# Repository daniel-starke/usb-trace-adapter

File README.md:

# USB Trace Adapter

The USB trace adapter can be used to trace/probe the USB communication of a
USB low speed, high speed or full speed connection with a logic analyzer
or oscilloscope.

# Structure

The USB trace adapter is build up of a USB 2.0 type A receptacle and
a USB 2.0 type A plug at both ends with a pin header in-between.
All lines are passed through between receptacle and plug as it.
The pin header offers easy access to VBUS, D+, D- and GND to allow
tracing and probing.

# Manufacturing

## PCB

Use the following parameters when ordering the PCB. Note that the values
have only been tested with JLCPCB so far. See [gerber files](hw/gerber).
- layers: 2
- base material: FR4
- dimensions: 21x18.8mm
- thickness: 1.6mm
- surface finish: lead free HASL
- impedance control: no
- outer copper weight: 1oz

With no special extras.

## BOM

- 1x [USB 2.0 type A plug](https://datasheet.lcsc.com/szlcsc/1811131825_Jing-Extension-of-the-Electronic-Co-C9739_C9739.pdf)
- 1x [USB 2.0 type A receptacle](https://datasheet.lcsc.com/lcsc/1912111437_SHOU-HAN-AF-90--WJDG_C456018.pdf)
- 1x [single row 4x pin header with 2.54mm pitch](https://datasheet.lcsc.com/lcsc/2008301604_Wcon-1125-1104G0S118C005_C721444.pdf)

All parts can be ordered at [LCSC](https://www.lcsc.com) (C9739, C456018 and C721444).

## Case

The case consists of a [bottom](print/case-Bottom.stl) and a
[top](print/case-Top.stl) part and can be 3D printed with PLA.
Other materials have not been tested.
Use the following print settings:
- layer height: 0.2mm
- nozzle diameter: 0.4mm
- infill: ≥15%
- perimeters: ≥3
- variable width perimeter generator (e.g. Arachne in PrusaSlicer)
- support: none
- print orientation: same as STL

Also recommended are:
- solid layers: ≥4
- infill pattern: adaptive cubic
- top/bottom fill pattern: monotonic

The [FreeCAD file](print/case.FCStd) contains a spreadsheet to easily change
tolerances to match the capabilities of the used 3D printer.

## Assembly

1. Solder the USB 2.0 type A plug at J1.
2. Solder the USB 2.0 type A receptacle at J2.
3. Solder the single row 4x pin header at J3.
4. Put the finished PCB into the bottom part of the case.
   The orientation is unambiguous.
   
5. Press the top part of the case onto the bottom part. Both parts should
   snap together. Make sure that the pin header hole is "pointing" towards the
   USB receptacle.

Note: All parts are soldered on the same side of the PCB.  
**Important:** Be sure that the USB connectors are fully inserted and
aligned when soldering. Especially when handling the USB plug.

## Connector Cable

It is possible to glue 4 female jumper cables and a small block of plastic
together to form a coded connector cable.

## Tracing

Sigrok provides ways to convert a logic trace into a PCAP file for further
analysis via Wireshark. See https://sigrok.org/blog/new-protocol-decoder-usb-request

### Example: Rigol DS1202Z-E with PulseView

This combination works fine for USB low speed (1.5 Mbps) and high speed (12 Mbps)
devices. However, it only captures a very short duration.

- Connect both probes to `D+` and `D-` and the ground to `GND`.
- Set the resolution to 5ms (trace length = 124ms, USB high speed) and the trigger to 1.5V.
- Set trigger type to `Pulse` on the channel with `D+` with less than 80ns.
- Run a single shot.
- Connect PulseView to Rigol DS1202Z-E and set its data source to `Memory`.
- Run the trace to collect the trace data.
- Set both channels to logic conversion via threshold (TTL).
- Add `USB request` decoder.

### Example: AZDelivery Logic Analyzer with sigrok

This combination works fine for USB low speed (1.5 Mbps) and may give some usable
results with USB high speed (12 Mbps) devices. Preferable is a logic analyzer with
48 MHz or more for USB high speed devices.

- Connect both probes to `D+` (CH0) and `D-` (CH1) and the ground to `GND`.
- `sigrok-cli -d fx2lafw -c samplerate=24M -C D0=DP,D1=DM --continuous -o trace.sr`.
- `sigrok-cli -i trace.sr -P usb_signalling:dp=DP:dm=DM,usb_packet,usb_request -B usb_request=pcap > trace.pcap`

Note that defining triggers does not work stable for this logic analyzer. The trace aborts shortly.

# License

See [LICENSE](LICENSE).  

# Contributions

No content contributions are accepted. Please file a bug report or feature request instead.  
This decision was made in consideration of the used license.

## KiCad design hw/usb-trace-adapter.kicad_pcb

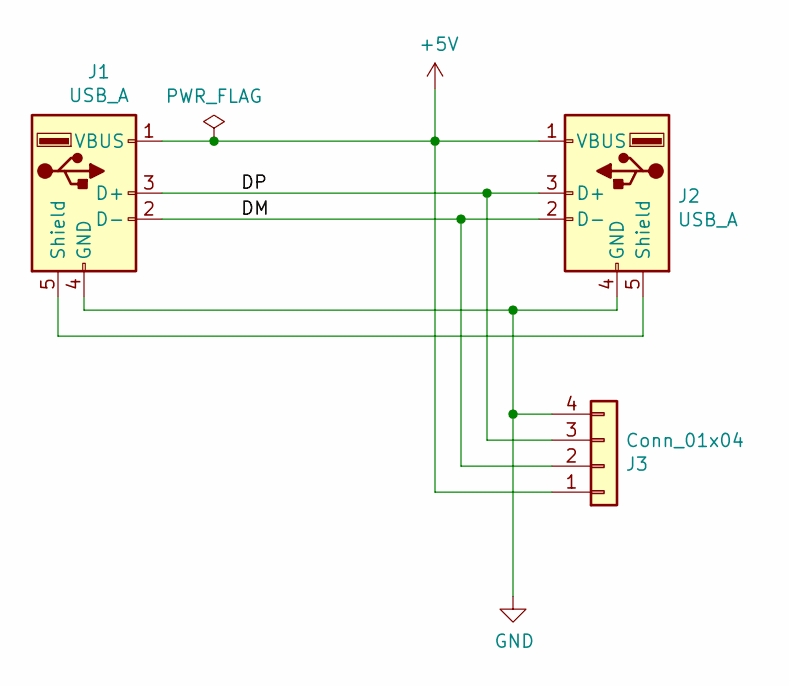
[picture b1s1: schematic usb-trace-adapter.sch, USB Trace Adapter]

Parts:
J1: USB_A; USB_A_TH_AM90; LCSC C9739
J2: USB_A; USB_A_Stewart_SS-52100-001_Horizontal; LCSC C456018
J3: Conn_01x04; PinHeader_1x04_P2.54mm_Vertical; LCSC C721444

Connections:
+5V: J1.1 (VBUS), J2.1 (VBUS), J3.1
/DM: J1.2 (D-), J2.2 (D-), J3.2
/DP: J1.3 (D+), J2.3 (D+), J3.3
GND: J1.4 (GND), J2.4 (GND), J3.4
unnamed: J1.5 (Shield), J2.5 (Shield)

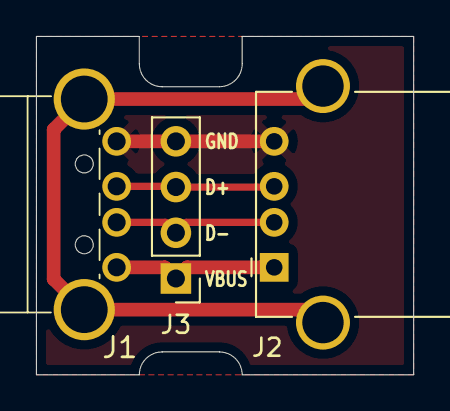
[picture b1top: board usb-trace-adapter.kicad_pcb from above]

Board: 2 copper layers, 21.0 x 18.8 mm, 3 parts (0 on the bottom side), 5 nets.

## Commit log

2023-09-01 Initial commit.
2023-09-01 Added funding info.
2023-09-01 Fixed wording in README.md.
2023-10-03 Added tracing examples to README.md.
2023-10-28 Change file hierarchy.
